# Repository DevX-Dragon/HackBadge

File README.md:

# HackBadge
**HackBadge** is an open-source badge, E-Ink Powered PCB badge desgined for hackathons, tech events or even maker events. Built around the ESP32. It provides low-power display capability, wireless connectivity and exapnsion for custom hardware.

## Features

- **ESP32 Microcontroller**: Integrated with WI-FI and Bluetooth LE (BLE) for networking, mesh communication, and OTA updates.
- **4.2 inch Waveshare E-Paper Display**: Ultra low-power, high visibility display that retains text and images even its powered off.
- **Programmale buttons**: Dedicated input buttons for navigating menus, switching displays or triggering a custom action.
- **Expaned GPIO Breakout**: Exposed GPIO pins allowing easy access for external sesors, LEDs and modules.

## How to DIY?

- Manufacture the PCB using the [Gerber Files](production/HackBadge.zip)
- Source the components from the [Bill of Material](bom.csv)
- Solder them according to the 
- Flash the firmware

## Firmware Flashing

- Open [Firmware.ino](firmware/firmware.ino) in Arduino IDE / Platoform IO
- Connect the ESP32 
- Flash the fimrware
- You should see informations on the Display
- Have fun tinkering with the firmware!

## Hardware Overview

### Schematics

### PCB Layout

### 3D View

## Bill of Materials (BOM)

| Part | Qty | Unit | Total | Where |
| --- | ---: | ---: | ---: | --- |
| PCB (JLCPCB) (w/ shipping) | 1 | $25.00 | $25.00 | JLCPCB |
| Waveshare E-Ink Display | 1 | $38.00 | $38.00 | [AliExpress](https://www.aliexpress.com/item/1005009085337626.html) |
| ESP32 | 1 | $7.00 | $7.00 | [AliExpress](https://www.aliexpress.com/item/1005012242722260.html) |
| RGB led | 1 | $0.50 | $0.50 | [Duino.lk LOCAL](https://www.duino.lk/product/rgb-led-5mm-water-clear-4-pin/) |
| switches | 5 | $0.10 | $0.50 | [Duino.lk LOCAL](https://www.duino.lk/product/12x12x13mm-touch-switch/) |

## Pinout Mapping

<details>
<summary>Click here to see the detailed pinout diagram</summary>

### E-Ink Display (8-Pin Connector)
| E-Ink Pin | Signal Name | ESP32 Board Pin | Description |
| :--- | :--- | :--- | :--- |
| **Pin 1** | VCC | 3.3V (Pin 1) | Power supply (+3.3V) |
| **Pin 2** | GND | GND (Pin 2) | Ground connection |
| **Pin 3** | DIN | D23 (Pin 15) | SPI Data Input (MOSI) |
| **Pin 4** | CLK | D18 (Pin 9) | SPI Clock Line |
| **Pin 5** | CS | D5 (Pin 8) | SPI Chip Select |
| **Pin 6** | DC | TX2 / GPIO17 (Pin 7) | Data / Command Control Line |
| **Pin 7** | RST | RX2 / GPIO16 (Pin 6) | Hardware Reset Line |
| **Pin 8** | BUSY | D4 / ADC2_CH0 (Pin 5) | Display Busy Signal Output |

---

### RGB LED (LED1)
| LED Pin | Signal Name | ESP32 Board Pin | Description |
| :--- | :--- | :--- | :--- |
| **Pin 1** | G (Green Anode) | DAC2 / ADC2_CH9 / D26 (Pin 24) | Green LED Anode Control |
| **Pin 2** | GND | GND (Pin 2 / 29) | Common Cathode Ground |
| **Pin 3** | R (Red Anode) | DAC1 / ADC2_CH8 / D25 (Pin 23) | Red LED Anode Control |
| **Pin 4** | B (Blue Anode) | ADC1_CH4 / D33 (Pin 22) | Blue LED Anode Control |

> [!TIP]
> Optional information to help a user be more successful.

---

### Push Buttons
| Button | Signal Name | ESP32 Board Pin | Description |
| :--- | :--- | :--- | :--- |
| **Button1** | GPIO13 | ADC2_CH4 / D13 (Pin 28) | Pushbutton Input (Switches to GND) |
| **Button2** | GPIO12 | ADC2_CH5 / D12 (Pin 27) | Pushbutton Input (Switches to GND) |
| **Button3** | GPIO14 | ADC2_CH6 / D14 (Pin 26) | Pushbutton Input (Switches to GND) |
| **Button4** | GPIO27 | ADC2_CH7 / D27 (Pin 25) | Pushbutton Input (Switches to GND) |
| **RESET** | EN | EN (Pin 16) | Hardware Reset Switch (Switches to GND) |

> [!TIP]
> The buttons can be assigned to any functions you like.

---

### Extra GPIO Breakout Header (J3 - 15-Pin Connector)
| J3 Pin | Signal Name | ESP32 Board Pin | Description |
| :--- | :--- | :--- | :--- |
| **Pin 1** | +5V | VIN (Pin 30) | +5V Power Rail |
| **Pin 2** | GND | GND (Pin 2) | Ground Rail |
| **Pin 3** | GPIO1 | TX0 / GPIO01 (Pin 13) | UART0 TX / General Purpose I/O |
| **Pin 4** | GPIO2 | D2 / ADC2_CH2 (Pin 4) | General Purpose I/O / ADC Input |
| **Pin 5** | GPIO3 | RX0 / GPIO03 (Pin 12) | UART0 RX / General Purpose I/O |
| **Pin 6** | GPIO15 | D15 / ADC2_CH3 (Pin 3) | General Purpose I/O / ADC Input |
| **Pin 7** | GPIO19 | D19 (Pin 10) | General Purpose I/O |
| **Pin 8** | VN | ADC1_CH3 / VN (Pin 18) | Input-only GPIO / ADC Input |
| **Pin 9** | GPIO32 | ADC1_CH4 / D32 (Pin 21) | General Purpose I/O / ADC Input |
| **Pin 10** | GPIO34 | ADC1_CH6 / D34 (Pin 19) | Input-only GPIO / ADC Input |
| **Pin 11** | GPIO35 | ADC1_CH7 / D35 (Pin 20) | Input-only GPIO / ADC Input |
| **Pin 12** | SDA/GPIO21 | D21 / SDA (Pin 11) | I2C Data Line (SDA) / General Purpose I/O |
| **Pin 13** | SCL/GPIO22 | D22 / SCL (Pin 14) | I2C Clock Line (SCL) / General Purpose I/O |
| **Pin 14** | GND | GND (Pin 29) | Ground Rail |
| **Pin 15** | +3.3V | 3.3V (Pin 1) | +3.3V Power Rail |

> [!TIP]
> The GPIO of the breakouts are marked in the PCB for easier access.

</details>

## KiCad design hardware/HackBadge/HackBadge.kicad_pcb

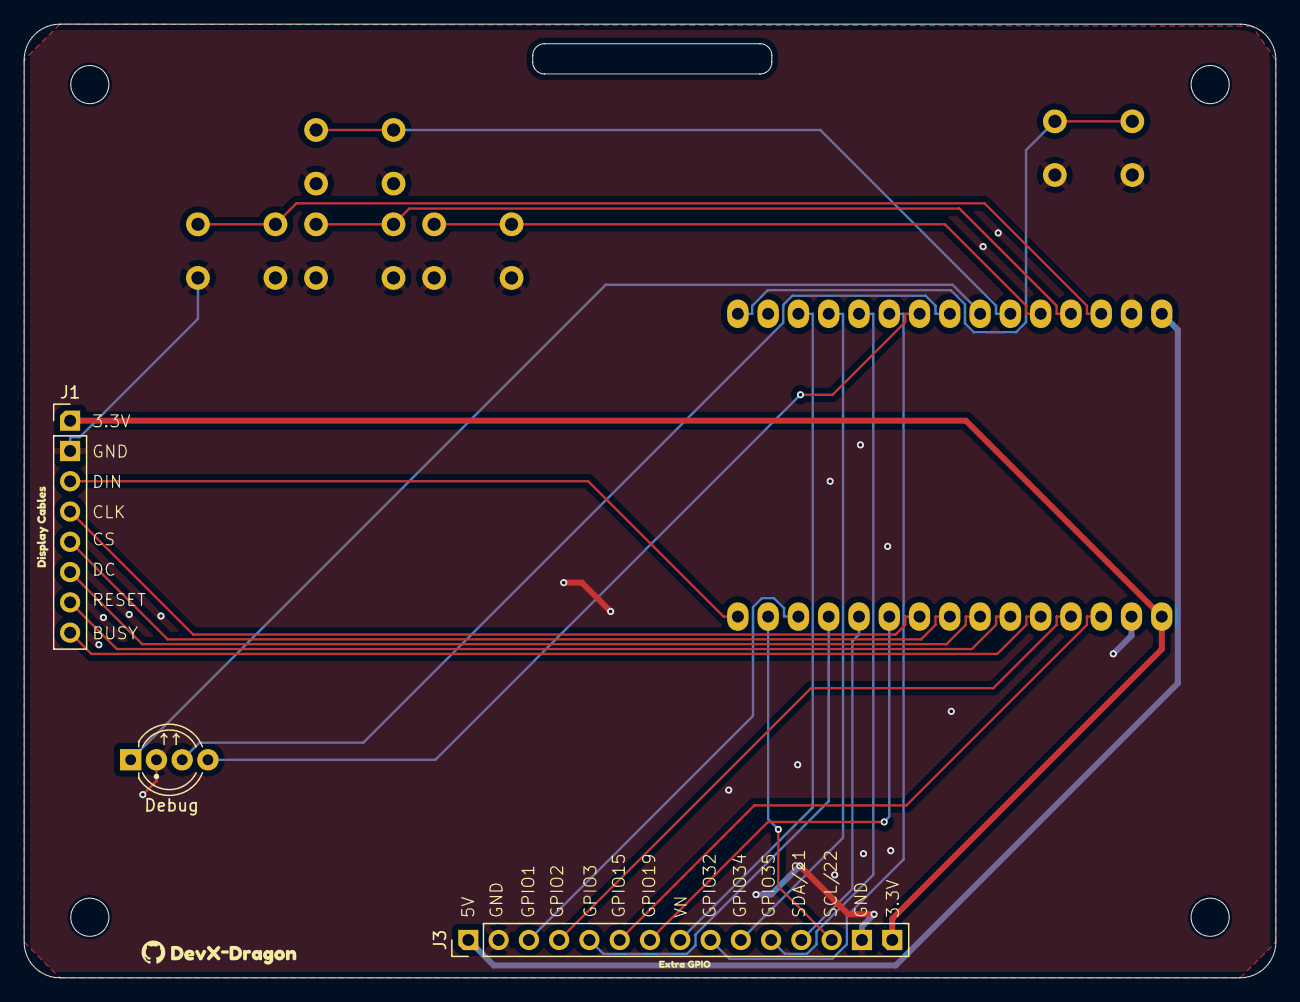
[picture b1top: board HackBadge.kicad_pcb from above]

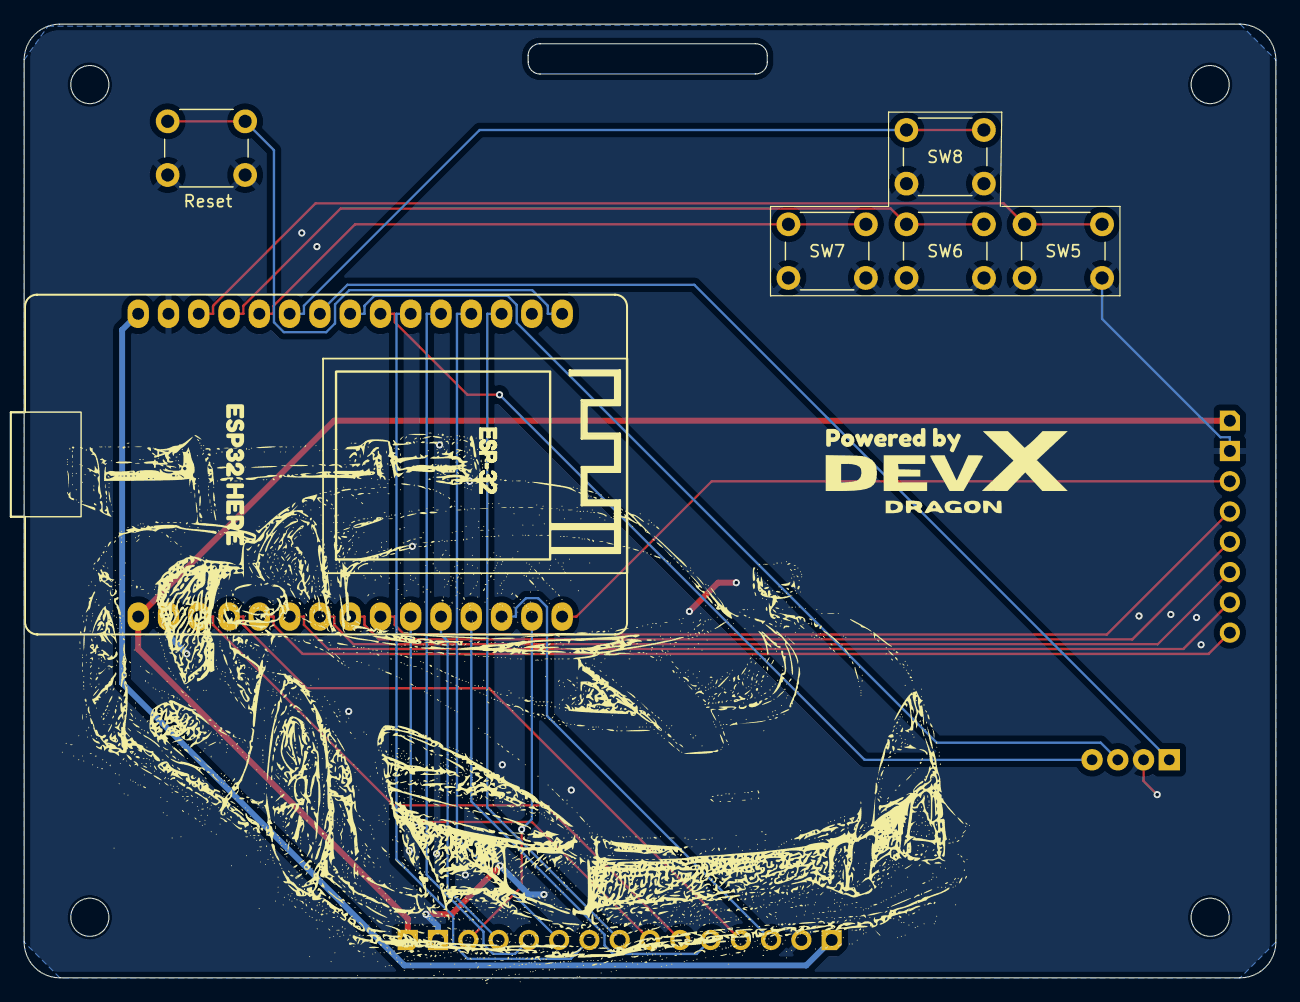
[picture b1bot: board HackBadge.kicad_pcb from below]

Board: 2 copper layers, 105.0 x 80.0 mm, 20 parts (9 on the bottom side), 28 nets.

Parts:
A1: ESP32_DevKit_V1_DOIT_30GPIOs; DOIT_ESP32_DEVKIT_30Pins
Debug : LED_5mm_RGB_Kcom_GKRB; LED_D5.0mm-4_RGB_Wide_Pins
J1: Conn_01x08; PinHeader_1x08_P2.54mm_Vertical
J3: Conn_01x15_Pin; PinHeader_1x15_P2.54mm_Vertical
M1, M2, M3, M4: MountingHole_3.2mm_M3
Reset : RESET; SW_PUSH_6mm_H5mm
S1: LOGO
SW5: Button1; SW_PUSH_6mm_H5mm
SW6: Button2; SW_PUSH_6mm_H5mm
SW7: Button3; SW_PUSH_6mm_H5mm
SW8: Button4; SW_PUSH_6mm_H5mm
g1: LOGO; Github
kibuzzard-6AC50D0B: G***; kibuzzard-6AC50D0B
kibuzzard-6AC50DDC: G***; kibuzzard-6AC50DDC
kibuzzard-6AC262A7: kibuzzard-6AC262A7
kibuzzard-6AC26231: kibuzzard-6AC26231
kibuzzard-6AC27300: G***; kibuzzard-6AC27300

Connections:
+3.3V: A1.1 (3.3V), J1.1, J3.15
+5V: A1.30 (VIN), J3.1
/BUSY: A1.5 (D4/ADC2_CH0), J1.8
/Chip-Select: A1.8 (D5), J1.5
/DATA-IN: A1.15 (D23), J1.3
/DC: A1.7 (TX2/GPIO17), J1.6
/GPIO1: A1.13 (TX0/GPIO1), J3.3
/GPIO2: A1.4 (D2/ADC2_CH2), J3.4
/GPIO3: A1.12 (RX0/GPIO3), J3.5
/GPIO15: A1.3 (D15/ADC2_CH3), J3.6
/GPIO19: A1.10 (D19), J3.7
/GPIO25/R: A1.23 (DAC1/ADC2_CH8/D25), Debug.3 (R)
/GPIO26/G: A1.24 (DAC2/ADC2_CH9/D26), Debug.1 (G)
/GPIO32: A1.21 (ADC1_CH4/D32), J3.9
/GPIO33/B: A1.22 (ADC1_CH4/D33), Debug.4 (B)
/GPIO34: A1.19 (ADC1_CH6/D34), J3.10
/GPIO35: A1.20 (ADC1_CH7/D35), J3.11
/RST: A1.6 (RX2/GPIO16), J1.7
/SCL/GPIO22: A1.14 (D22/SCL), J3.13
/SDA/GPIO21: A1.11 (D21/SDA), J3.12
/SPI-CLOCK: A1.9 (D18), J1.4
/VN: A1.18 (ADC1_CH3/VN), J3.8
GND: A1.2 (GND), A1.29 (GND), Debug.2 (A), J1.2, J3.2, J3.14, Reset.2, SW5.2, SW6.2, SW7.2, SW8.2
unnamed: A1.28 (ADC2_CH4/D13), SW5.1
unnamed: A1.27 (ADC2_CH5/D12), SW6.1
unnamed: A1.26 (ADC2_CH6/D14), SW7.1
unnamed: A1.25 (ADC2_CH7/D27), SW8.1
unnamed: A1.16 (EN), Reset.1
